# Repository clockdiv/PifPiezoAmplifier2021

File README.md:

# PifPiezoAmplifier2021
 a tiny piezo preamp built during pif camp 2021

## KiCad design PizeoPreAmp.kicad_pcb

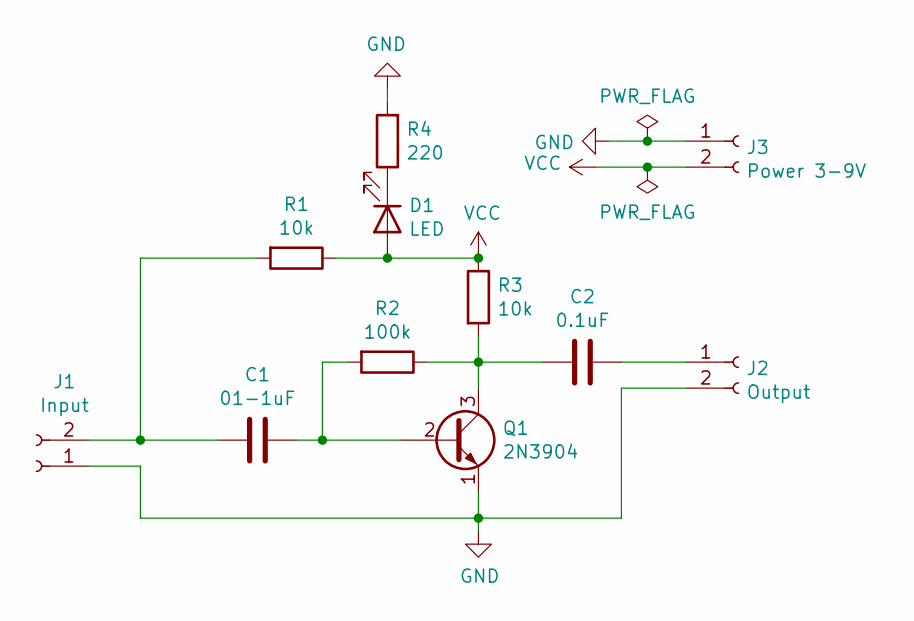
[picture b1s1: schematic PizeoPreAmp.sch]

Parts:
C1: 01-1uF; C_Axial_L5.1mm_D3.1mm_P7.50mm_Horizontal
C2: 0.1uF; C_Axial_L5.1mm_D3.1mm_P7.50mm_Horizontal
D1: LED; LED_D3.0mm
J1: Input; PinHeader_1x02_P2.54mm_Vertical
J2: Output; PinHeader_1x02_P2.54mm_Vertical
J3: Power 3-9V; PinHeader_1x02_P2.54mm_Vertical
Q1: 2N3904; TO-92_Inline
R1, R3: 10k; R_Axial_DIN0207_L6.3mm_D2.5mm_P7.62mm_Horizontal
R2: 100k; R_Axial_DIN0207_L6.3mm_D2.5mm_P7.62mm_Horizontal
R4: 220; R_Axial_DIN0207_L6.3mm_D2.5mm_P7.62mm_Horizontal

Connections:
GND: J1.1, J2.2, J3.1, Q1.1 (E), R4.2
unnamed: C1.1, Q1.2 (B), R2.2
unnamed: C1.2, J1.2, R1.2
unnamed: C2.1, J2.1
unnamed: C2.2, Q1.3 (C), R2.1, R3.2
unnamed: D1.1 (K), R4.1
VCC: D1.2 (A), J3.2, R1.1, R3.1

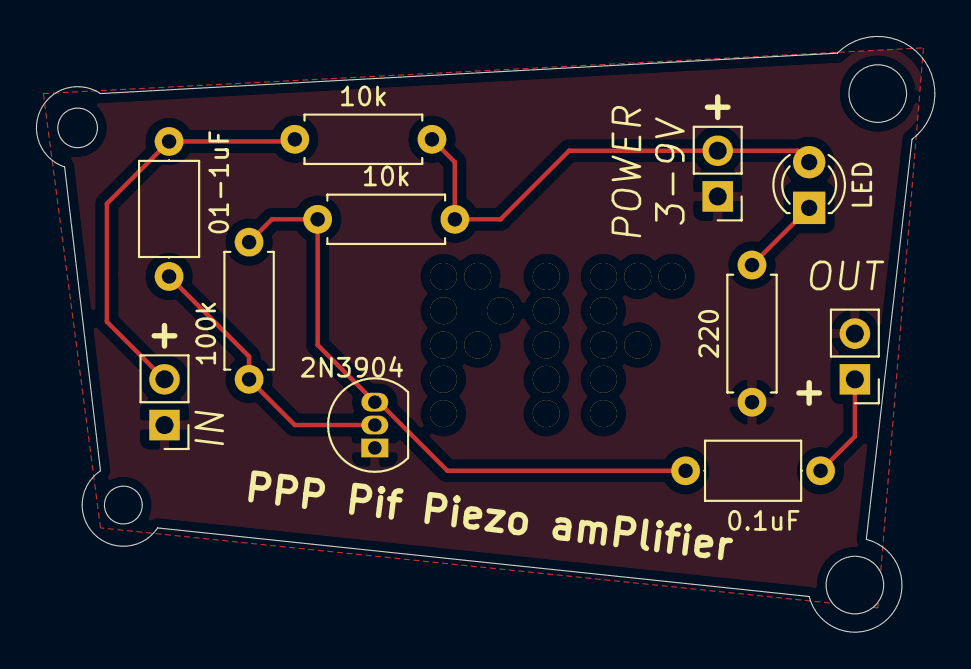
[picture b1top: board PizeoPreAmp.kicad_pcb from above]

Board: 2 copper layers, 49.9 x 33.1 mm, 11 parts (0 on the bottom side), 7 nets.
